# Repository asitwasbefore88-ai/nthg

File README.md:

# MY-PCB

## Schematic

## PCB

## How to build
Just order the PCB & components, open up the KiCAD file and build it accordingly.

## BOM
- 1 	Battery holder
- 3 	470 Resistor
- 1 	Push Button
- 3 LEDs

Made by ME

Made as a part of http://solder.hackclub.com/!

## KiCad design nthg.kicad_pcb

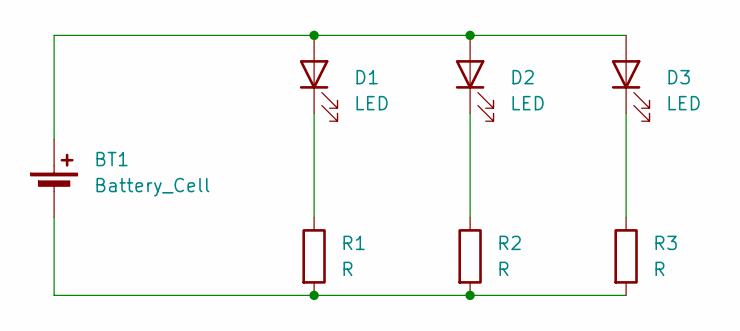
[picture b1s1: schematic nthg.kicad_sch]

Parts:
BT1: Battery_Cell; BatteryHolder_Keystone_3034_1x20mm
D1, D2, D3: LED; LED_D5.0mm
R1, R2, R3: R; R_Axial_DIN0207_L6.3mm_D2.5mm_P7.62mm_Horizontal

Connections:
unnamed: BT1.1 (+), D1.2 (A), D2.2 (A), D3.2 (A)
unnamed: BT1.2 (-), R1.2, R2.2, R3.2
unnamed: D1.1 (K), R1.1
unnamed: D2.1 (K), R2.1
unnamed: D3.1 (K), R3.1

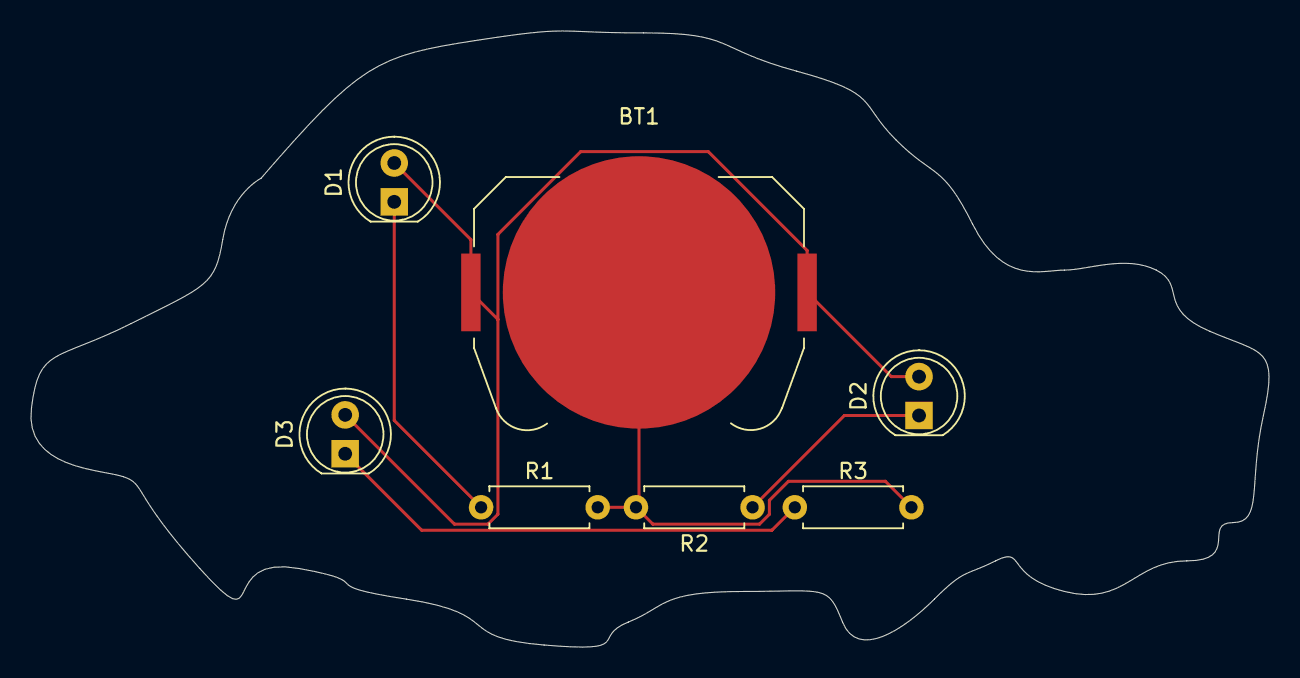
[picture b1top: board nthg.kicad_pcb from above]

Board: 2 copper layers, 80.9 x 40.3 mm, 7 parts (0 on the bottom side), 5 nets.
